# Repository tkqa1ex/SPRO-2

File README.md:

# SPRO-2: Motor Control & Generator Project

## 🟦 Project Overview
This repository contains the hardware designs and firmware for our university semester project (SPRO-2).

---

## 📂 Repository Structure

### 🔌 [Hardware](./motor-PCB)
The hardware is designed in **KiCad** and is split into three main modules:
* **Control Board:** The "brains" of the operation, handling logic and signal processing.
* **Generator Board:** Responsible for power generation and distribution.
* **Current Sensor Test Board:** A dedicated board for validating the current sensing circuitry before full integration.

### 💻 [Firmware](./Firmware)
*(Coming Soon)*
The firmware will handle the motor control algorithms, sensor data acquisition, and communication logic.

---

## 🛠 Tech Stack
* **PCB Design:** KiCad 10.0
* **Firmware:** C / Arduino
* **Documentation:** LaTeX

---

## 👥 Team Members
* **Alexander (tkqa1ex)**
* **David (floppy)**
* [Name 3] - [Role]

---

## 🚀 Getting Started
1. **Clone the repo:**
   ```bash
   git clone [https://github.com/tkqa1ex/SPRO-2.git](https://github.com/tkqa1ex/SPRO-2.git)

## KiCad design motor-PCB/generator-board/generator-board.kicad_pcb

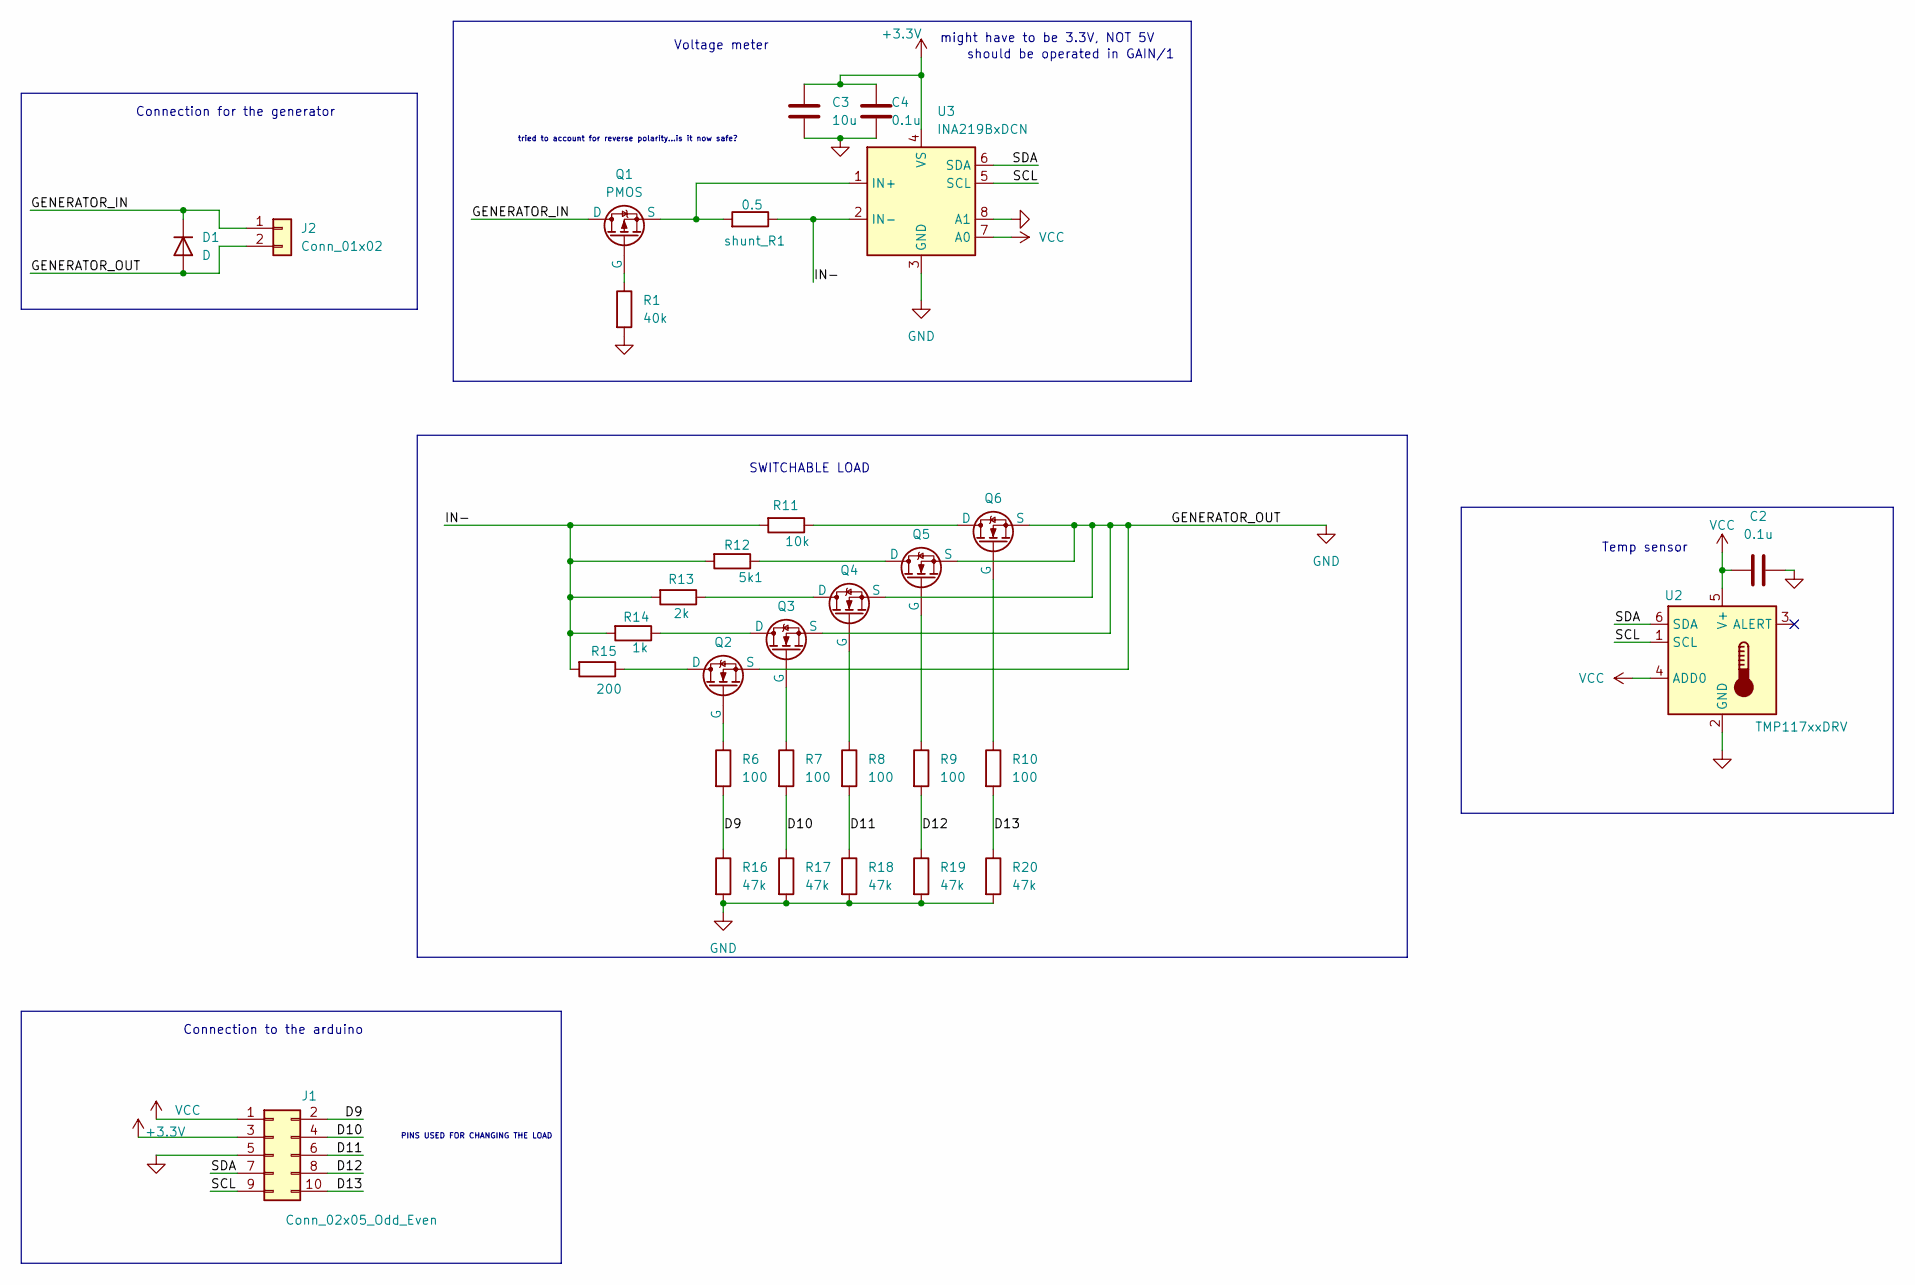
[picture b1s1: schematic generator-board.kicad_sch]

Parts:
C2, C4: 0.1u; CP_Radial_D10.0mm_P5.00mm
C3: 10u; CP_Radial_D10.0mm_P5.00mm
D1: D; D_DO-41_SOD81_P10.16mm_Horizontal
J1: Conn_02x05_Odd_Even; PinHeader_2x05_P2.54mm_Vertical
J2: Conn_01x02; PinHeader_1x02_P2.54mm_Vertical
Q1: PMOS; TO-220-3_Vertical
Q2, Q3, Q4, Q5, Q6: NMOS_GDS; TO-220-3_Vertical
R1: 40k; R_Axial_DIN0207_L6.3mm_D2.5mm_P10.16mm_Horizontal
R6, R7, R8, R9, R10: 100; R_Axial_DIN0207_L6.3mm_D2.5mm_P10.16mm_Horizontal
R11: 10k; R_Axial_DIN0207_L6.3mm_D2.5mm_P10.16mm_Horizontal
R12: 5k1; R_Axial_DIN0207_L6.3mm_D2.5mm_P10.16mm_Horizontal
R13: 2k; R_Axial_DIN0207_L6.3mm_D2.5mm_P10.16mm_Horizontal
R14: 1k; R_Axial_DIN0207_L6.3mm_D2.5mm_P10.16mm_Horizontal
R15: 200; R_Axial_DIN0207_L6.3mm_D2.5mm_P10.16mm_Horizontal
R16, R17, R18, R19, R20: 47k; R_Axial_DIN0207_L6.3mm_D2.5mm_P10.16mm_Horizontal
U2: TMP117xxDRV; WSON-6-1EP_2x2mm_P0.65mm_EP1x1.6mm
U3: INA219BxDCN; SOT-23-8
shunt_R1: 0.5; R_Axial_DIN0207_L6.3mm_D2.5mm_P10.16mm_Horizontal

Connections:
+3.3V: C3.1, C4.1, J1.3, U3.4 (VS)
/D9: J1.2, R6.2, R16.1
/D10: J1.4, R7.2, R17.1
/D11: J1.6, R8.2, R18.1
/D12: J1.8, R9.2, R19.1
/D13: J1.10, R10.2, R20.1
/GENERATOR_IN: D1.1 (K), J2.1, Q1.2 (D)
/IN-: R11.2, R12.2, R13.2, R14.2, R15.2, U3.2 (IN-), shunt_R1.1
/SCL: J1.9, U2.1 (SCL), U3.5 (SCL)
/SDA: J1.7, U2.6 (SDA), U3.6 (SDA)
GND: C2.2, C3.2, C4.2, D1.2 (A), J1.5, J2.2, Q2.3 (S), Q3.3 (S), Q4.3 (S), Q5.3 (S), Q6.3 (S), R1.2, R16.2, R17.2, R18.2, R19.2, R20.2, U2.2 (GND), U3.3 (GND), U3.8 (A1)
unnamed: Q1.1 (G), R1.1
unnamed: Q1.3 (S), U3.1 (IN+), shunt_R1.2
unnamed: Q2.2 (D), R15.1
unnamed: Q2.1 (G), R6.1
unnamed: Q3.2 (D), R14.1
unnamed: Q3.1 (G), R7.1
unnamed: Q4.2 (D), R13.1
unnamed: Q4.1 (G), R8.1
unnamed: Q5.2 (D), R12.1
unnamed: Q5.1 (G), R9.1
unnamed: Q6.2 (D), R11.1
unnamed: Q6.1 (G), R10.1
VCC: C2.1, J1.1, U2.4 (ADD0), U2.5 (V+), U3.7 (A0)

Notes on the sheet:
Voltage meter
tried to account for reverse polarity...is it now safe?
might have to be 3.3V, NOT 5V
Temp sensor
SWITCHABLE LOAD
Connection for the generator
should be operated in GAIN/1
Connection to the arduino
PINS USED FOR CHANGING THE LOAD

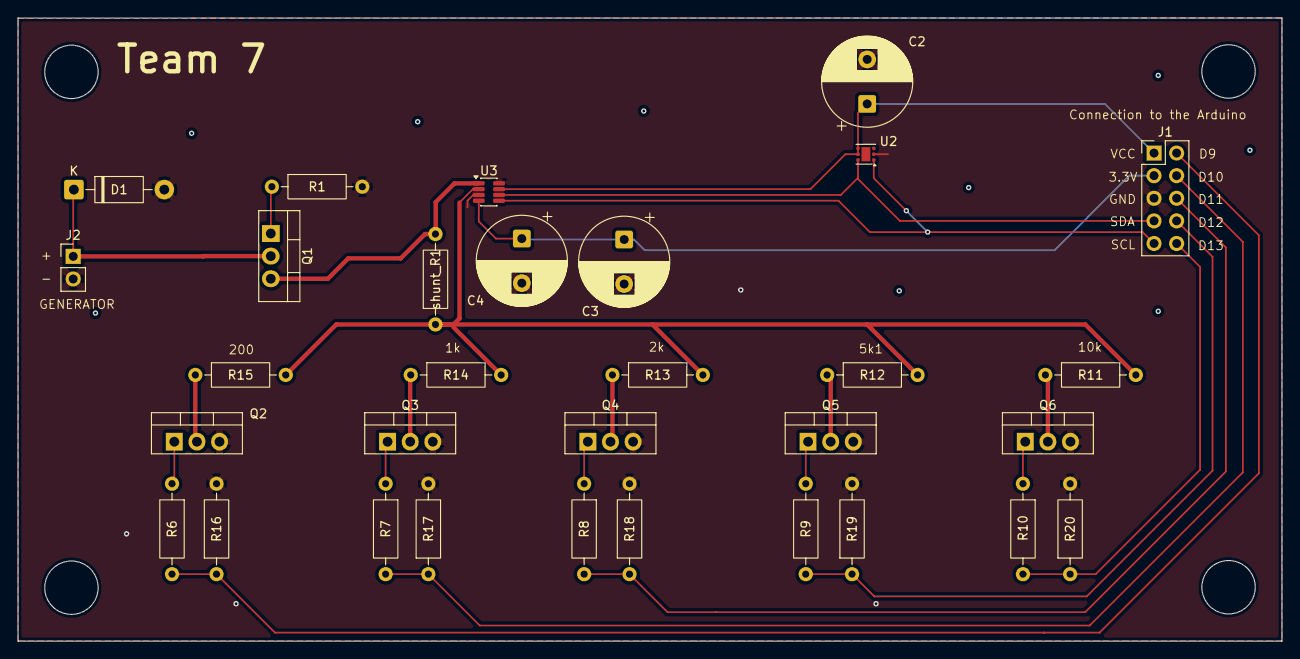
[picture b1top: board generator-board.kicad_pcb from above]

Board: 2 copper layers, 142.0 x 70.0 mm, 31 parts (0 on the bottom side), 24 nets.

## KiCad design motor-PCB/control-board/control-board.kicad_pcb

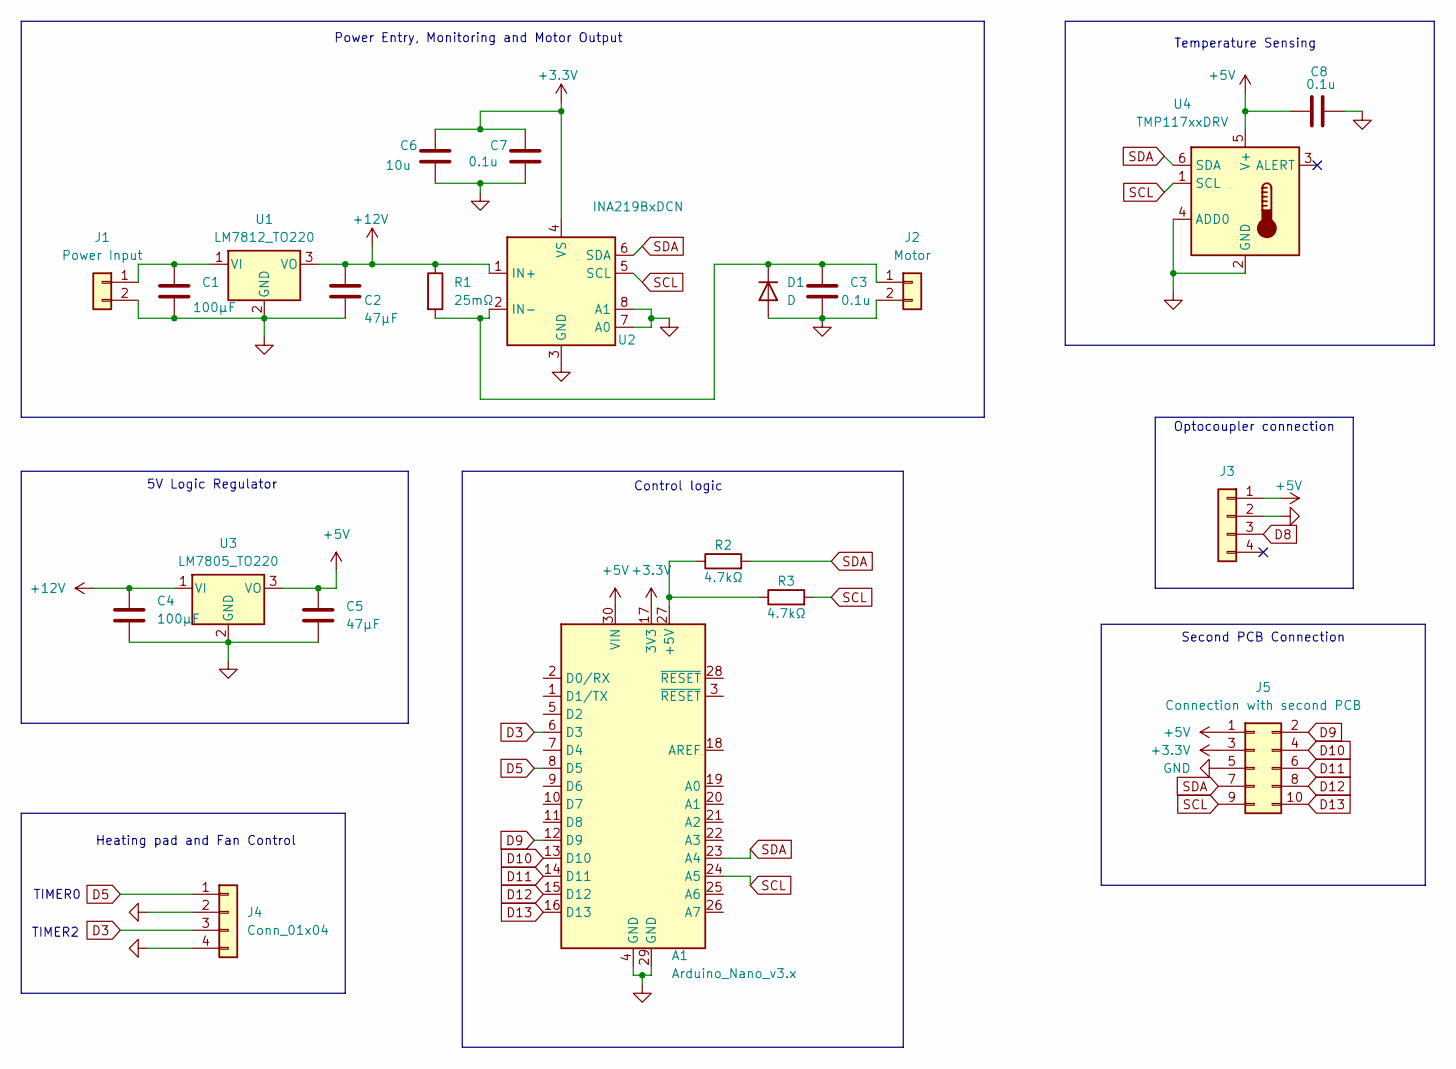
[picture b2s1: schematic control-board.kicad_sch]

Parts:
A1: Arduino_Nano_v3.x; Arduino_Nano
C1, C4: 100µF; CP_Radial_D8.0mm_P3.50mm
C2, C5: 47µF; CP_Radial_D6.3mm_P2.50mm
C3, C7, C8: 0.1u; C_Disc_D5.0mm_W2.5mm_P2.50mm
C6: 10u; CP_Radial_D5.0mm_P2.00mm
D1: D; D_DO-41_SOD81_P10.16mm_Horizontal
J1: Power Input; 1x02_P2.54mm_Horizontal
J2: Motor; 1x02_P2.54mm_Horizontal
J3: Optocoupler; PinHeader_1x04_P2.54mm_Vertical
J4: Conn_01x04; 1x04_P2.54mm_Horizontal
J5: Connection with second PCB; PinHeader_2x05_P2.54mm_Vertical
R1: 25mΩ; R_Axial_DIN0414_L11.9mm_D4.5mm_P15.24mm_Horizontal
R2: 4.7kΩ; R_Axial_DIN0207_L6.3mm_D2.5mm_P10.16mm_Horizontal
R3: 4.7kΩ; R_Axial_DIN0207_L6.3mm_D2.5mm_P7.62mm_Horizontal
U1: LM7812_TO220; TO-220-3_Vertical
U2: INA219BxDCN; SOT-23-8
U3: LM7805_TO220; TO-220-3_Vertical
U4: TMP117xxDRV; WSON-6-1EP_2x2mm_P0.65mm_EP1x1.6mm

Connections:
+3.3V: A1.17 (3V3), C6.1, C7.1, J5.3, U2.4 (VS)
+5V: A1.30 (VIN), C5.1, C8.1, J3.1, J5.1, U3.3 (VO), U4.5 (V+)
+12V: C2.1, C4.1, R1.1, U1.3 (VO), U2.1 (IN+), U3.1 (VI)
D3: A1.6 (D3), J4.3
D5: A1.8 (D5), J4.1
D8: J3.3
D9: A1.12 (D9), J5.2
D10: A1.13 (D10), J5.4
D11: A1.14 (D11), J5.6
D12: A1.15 (D12), J5.8
D13: A1.16 (D13), J5.10
GND: A1.4 (GND), A1.29 (GND), C1.2, C2.2, C3.2, C4.2, C5.2, C6.2, C7.2, C8.2, D1.2 (A), J1.2, J2.2, J3.2, J4.2, J4.4, J5.5, U1.2 (GND), U2.3 (GND), U2.7 (A0), U2.8 (A1), U3.2 (GND), U4.2 (GND), U4.4 (ADD0)
unnamed: A1.27 (+5V), R2.1, R3.1
unnamed: C3.1, D1.1 (K), J2.1, R1.2, U2.2 (IN-)
unnamed: C1.1, J1.1, U1.1 (VI)
SCL: A1.24 (A5), J5.9, R3.2, U2.5 (SCL), U4.1 (SCL)
SDA: A1.23 (A4), J5.7, R2.2, U2.6 (SDA), U4.6 (SDA)

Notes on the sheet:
TIMER2
Temperature Sensing
TIMER0
Control logic
Optocoupler connection
Power Entry, Monitoring and Motor Output
Second PCB Connection
5V Logic Regulator
Heating pad and Fan Control

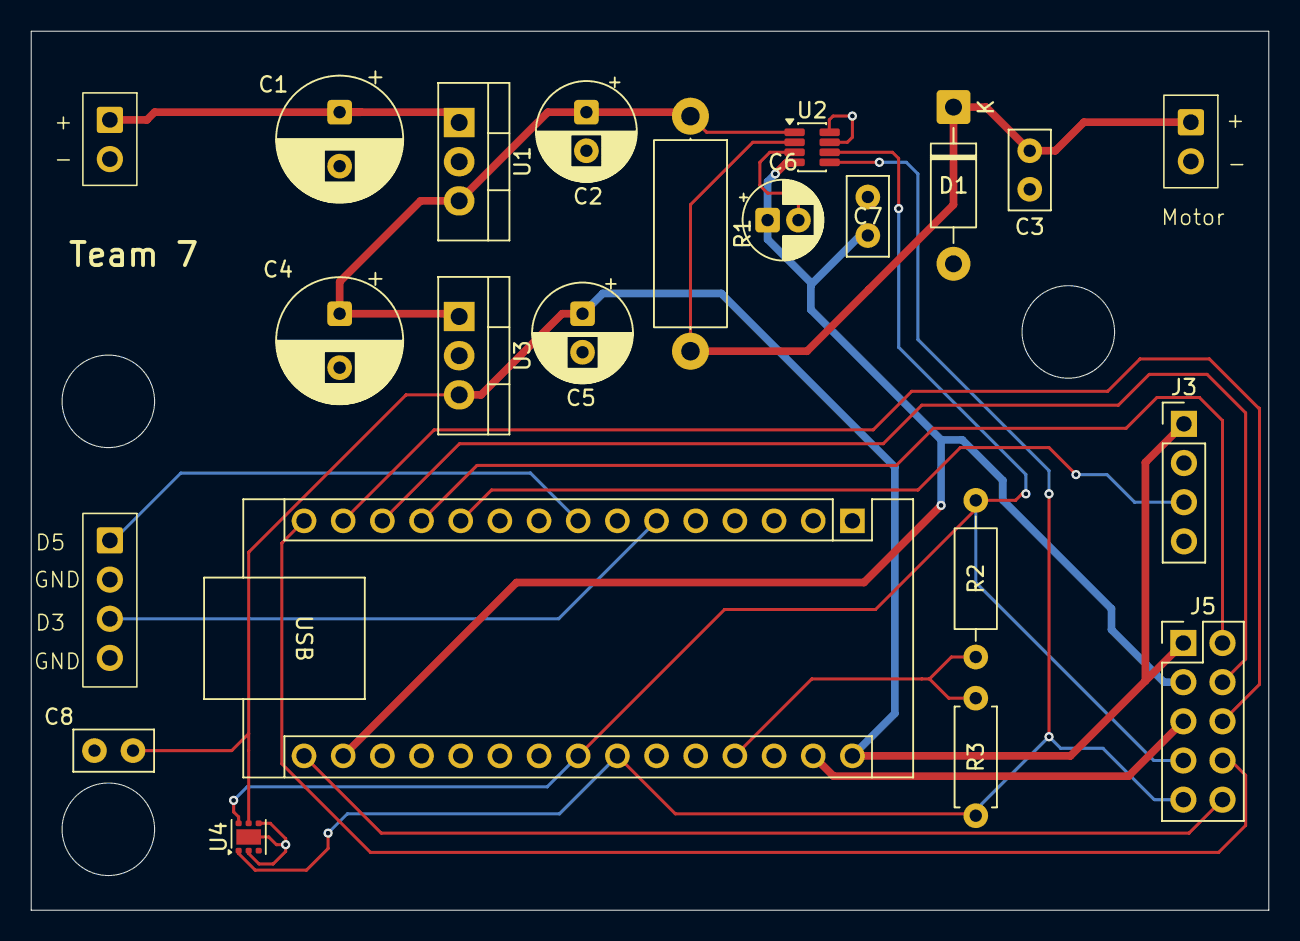
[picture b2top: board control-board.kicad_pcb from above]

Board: 2 copper layers, 80.2 x 57.0 mm, 22 parts (0 on the bottom side), 16 nets.

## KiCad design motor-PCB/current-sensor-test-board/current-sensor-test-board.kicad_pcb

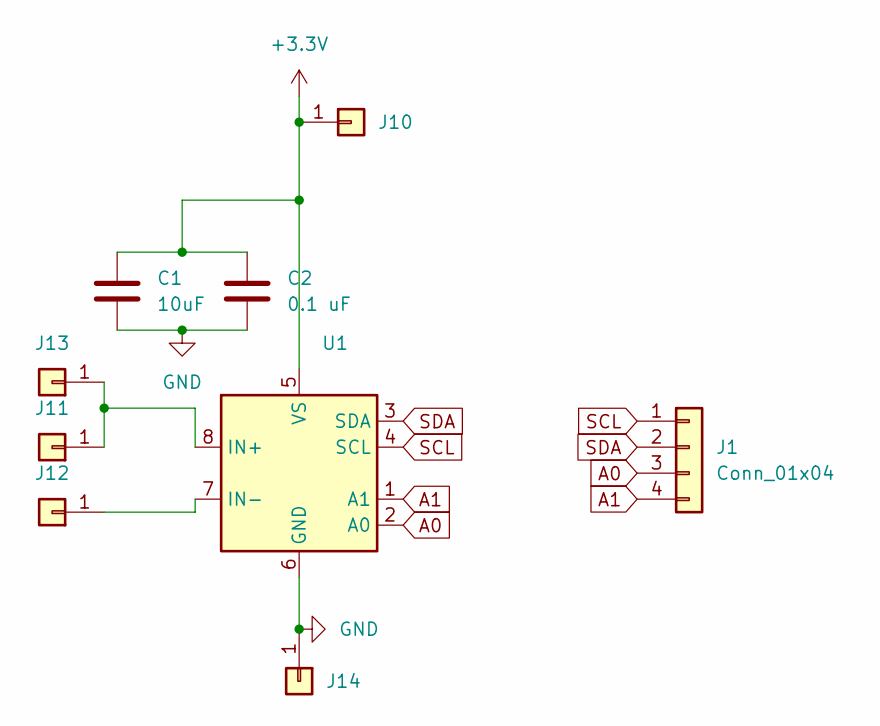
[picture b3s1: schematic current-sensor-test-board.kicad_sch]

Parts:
C1: 10uF; CP_Radial_D5.0mm_P2.00mm
C2: 0.1 uF; C_Disc_D5.0mm_W2.5mm_P2.50mm
J1: Conn_01x04; PinHeader_1x04_P2.54mm_Vertical
J10, J13, J14: Conn_01x01; PinHeader_1x01_P2.54mm_Vertical
J11, J12: Conn_01x01; PinSocket_1x01_P2.54mm_Vertical
U1: INA219AxD; SOIC-8_3.9x4.9mm_P1.27mm

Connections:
+3.3V: C1.2, C2.1, J10.1 (Pin_1_1), U1.5 (VS)
A0: J1.3, U1.2 (A0)
A1: J1.4, U1.1 (A1)
GND: C1.1, C2.2, J14.1 (Pin_1_1), U1.6 (GND)
unnamed: J11.1 (Pin_1_1), J13.1 (Pin_1_1), U1.8 (IN+)
unnamed: J12.1 (Pin_1_1), U1.7 (IN-)
SCL: J1.1, U1.4 (SCL)
SDA: J1.2, U1.3 (SDA)

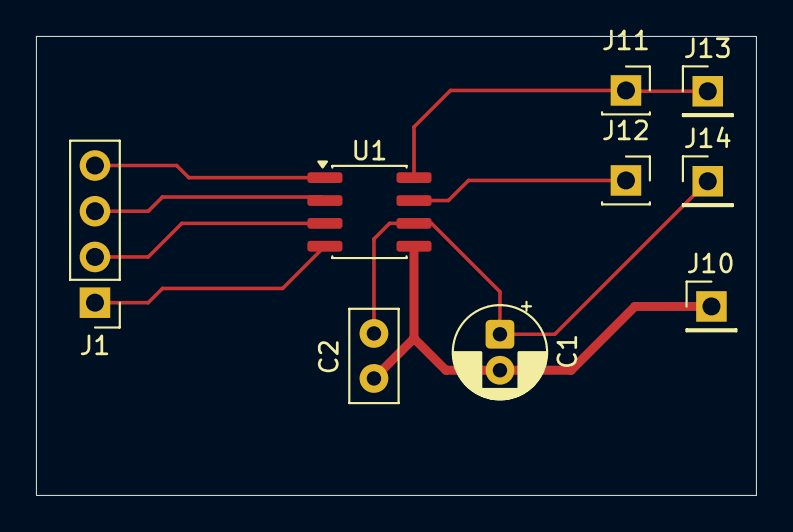
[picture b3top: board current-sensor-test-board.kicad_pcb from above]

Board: 2 copper layers, 40.0 x 25.5 mm, 9 parts (0 on the bottom side), 8 nets.

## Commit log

2026-05-11 Initial commit: Added PCB folders and project structure
2026-05-11 Cleanup: Remove .DS_Store files and ignore them
2026-05-11 Initialize README with project details
    Add project overview, repository structure, tech stack, team members, and getting started instructions to README.
2026-05-11 Revise README with updated tech stack and overview
    Updated project overview and tech stack details.
2026-05-16 Update README.md
    updated the members list :)
2026-05-16 Create temp
2026-05-17 added a missing capacitor in the control-board. Added pins to be able to control the heating pad and fan and text. In the generator changed the transistor layout and also added text
2026-05-18 forgot to change the layout of the pmos so fixed that
2026-05-19 Just forgot to update the ground mask :)
2026-05-20 Fixed SDA and SCL connections
2026-05-22 -the code at long last
2026-05-23 Add files via upload
    added the code for the 2nd arduino to control the heating pad and the fan
2026-05-25 Added the optocoupler functionality + finished the functions
    Now we just gotta figure out the current readings for the generator
2026-05-26 Forgot to include the new optocoupler file
2026-05-26 Added the opto functionality and libraries
2026-05-27 Current code finally works
2026-05-27 Final Control-Board
2026-05-28 Final Code
2026-05-29 Add files via upload
    added the code with more comments and hopefullt less romanian :))
2026-05-29 Final Code
    added timer for the duration of the test
2026-05-30 Final MATLAB Code
2026-05-31 Add files via upload
    Forgot to make the adc not change anymore after a button press
2026-05-31 Added more comments
2026-05-31 Checked the ml communication with timers
2026-05-31 Data from the tests
2026-05-31 Delete Code directory
    bye
